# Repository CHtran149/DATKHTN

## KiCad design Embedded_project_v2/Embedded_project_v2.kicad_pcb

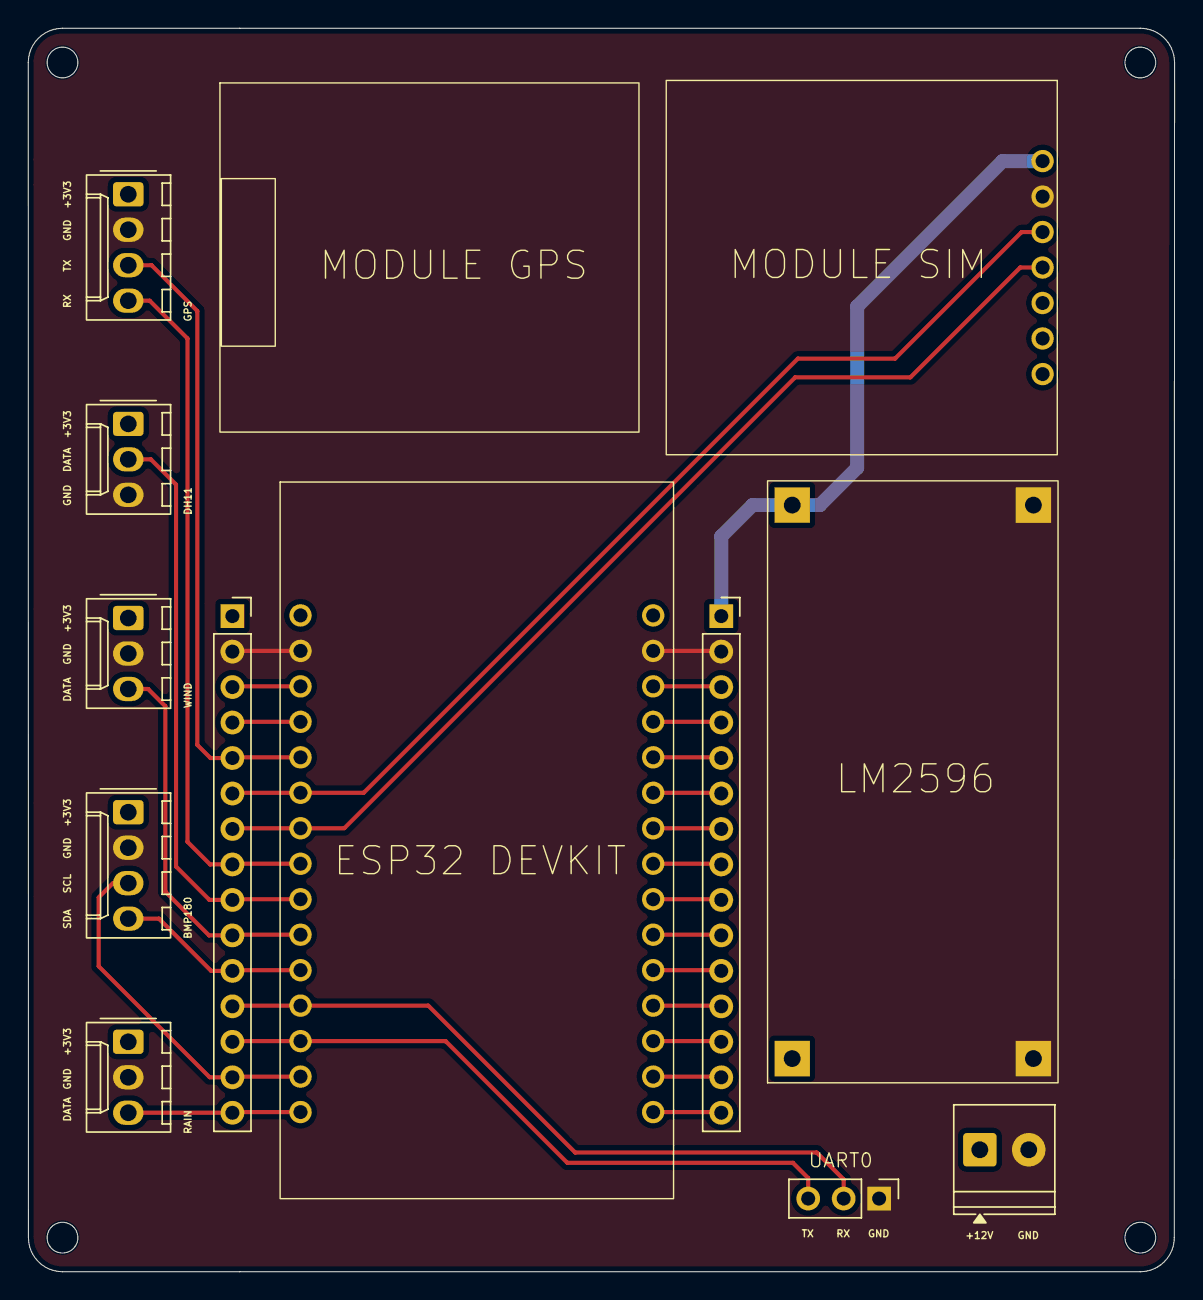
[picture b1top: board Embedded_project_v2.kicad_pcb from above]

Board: 2 copper layers, 82.1 x 89.0 mm, 12 parts (0 on the bottom side), 30 nets.

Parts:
J1: POWER IN; TerminalBlock_Phoenix_PT-1,5-2-3.5-H_1x02_P3.50mm_Horizontal
J2: TEMP,HUM SENSOR; Molex_KK-254_AE-6410-03A_1x03_P2.54mm_Vertical
J3: BMP180; Molex_KK-254_AE-6410-04A_1x04_P2.54mm_Vertical
J4: WIND SENSOR; Molex_KK-254_AE-6410-03A_1x03_P2.54mm_Vertical
J5: GPS; Molex_KK-254_AE-6410-04A_1x04_P2.54mm_Vertical
J6: RAIN SENSOR; Molex_KK-254_AE-6410-03A_1x03_P2.54mm_Vertical
J8, J9: Conn_01x15_Pin; PinSocket_1x15_P2.54mm_Vertical
J10: UART0; PinHeader_1x03_P2.54mm_Vertical
U1: Module LM2596
U2: DOIT_ESP32_DEVKIT_V1
U3: TDM-A7680C

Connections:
+3V3: J2.1, J3.1, J4.1, J5.1, J6.1, J8.1, U2.1 (3V3)
+5V: J9.1, U1.3 (OUT+), U2.16 (Vin), U3.1 (VCC)
+12V: J1.1, U1.1 (IN+)
/BMP180_SCL: J3.3, J8.14, U2.14 (D22)
/BMP180_SDA: J3.4, J8.11, U2.11 (D21)
/DHT11_DATA: J2.2, J8.9, U2.9 (D18)
/GMS_RX: J8.7, U2.7 (D17/TX2), U3.4 (RX)
/GMS_TX: J8.6, U2.6 (D16/RX2), U3.3 (TX)
/GPS_RX: J5.4, J8.8, U2.8 (D5)
/GPS_TX: J5.3, J8.5, U2.5 (D4)
/RAIN_DATA: J6.3, J8.15, U2.15 (D23)
/RX0: J8.12, J10.2, U2.12 (D3/RX0)
/TX0: J8.13, J10.3, U2.13 (D1/TX0)
/WIND_DATA: J4.3, J8.10, U2.10 (D19)
GND: J1.2, J2.3, J3.2, J4.2, J5.2, J6.2, J8.2, J9.2, J10.1, U1.2 (IN-), U1.4 (OUT-), U2.2 (GND), U2.17 (GND), U3.2 (GND)
unnamed: J8.3, U2.3 (D15)
unnamed: J8.4, U2.4 (D2)
unnamed: J9.3, U2.18 (D13)
unnamed: J9.4, U2.19 (D12)
unnamed: J9.5, U2.20 (D14)
unnamed: J9.6, U2.21 (D27)
unnamed: J9.7, U2.22 (D26)
unnamed: J9.8, U2.23 (D25)
unnamed: J9.9, U2.24 (D33)
unnamed: J9.10, U2.25 (D32)
unnamed: J9.11, U2.26 (D35)
unnamed: J9.12, U2.27 (D34)
unnamed: J9.13, U2.28 (D39/VN)
unnamed: J9.14, U2.29 (D36/VP)
unnamed: J9.15, U2.30 (EN)

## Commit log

2026-02-01 thêm code lần đầu tiên
2026-02-01 sửa lại cấu trúc code dự án
2026-02-03 Sửa lại Windspeed
2026-02-04 thêm task_sensor vào
2026-02-28 thêm task_processing
2026-02-28 Thêm 2 task là TaskFSM và TaskComm
2026-02-28 Chỉnh sửa Task_Comm
2026-03-02 thêm 2 task mới là TaskBlynk và TaskClould nhưng vẫn chưa hoàn thiện cần chỉnh sửa thêm
2026-03-12 Sửa lại thư viện GSM.h/.cpp và TaskComm.cpp (thêm yêu cầu 2 chiều từ SIM)
2026-03-12 TaskCould đang hoàn thiện
2026-03-13 sửa lại task_blynk và cập nhật dữ liệu lên app
2026-03-18 Đã chạy thành công hiển thị GPS lên log
2026-03-18 đưa GPS hiển thị lên blynk_app
2026-03-20 sửa thêm thư viện riêng và main.cpp
2026-03-25 thử và chạy thành công
2026-03-29 sửa phần request trong TaskComm
2026-03-29 đang hoàn thành task_comm
2026-03-29 thêm mới taskComm
2026-03-29 thêm gửi dữ liệu theo chu kì
2026-03-30 thay đổi wifi báo cáo
2026-04-01 thay đổi sơ đồ chân các cảm biến
2026-04-01 sửa lại thư viện cho GPS và đã chạy thành công
2026-04-02 đã gửi GMS thành công
2026-04-02 Thêm đặt ngưỡng cảnh báo bằng SMS chưa test.
2026-04-02 thêm chức năng gửi cả ngưỡng cảnh báo về trong TaskComm
2026-04-02 thay doi so dien thoai moi
2026-04-02 Cải thiện TaskComm về phần set ngưỡng
2026-04-02 TaskComm
2026-04-02 chỉnh sửa TaskComm và cả GSM.cpp
2026-04-02 Khắc phục lỗi thiếu dữ liệu khi SET và REQ
2026-04-05 triển khai task_cloud
2026-04-05 cập nhật task_cloud 5 phút gửi 1 lần
2026-05-09 thêm điều khiển từ blynk xuống hệ thống
2026-05-09 thay đổi 1 vài vấn đề cập nhật taskblynk, cloud,comm
2026-05-09 Đồng bộ ngưỡng của Blynk với Cloud
2026-05-09 Đồng bộ giữa task_comm và task_blynk (slider)
2026-05-13 điều chỉnh các thông số gửi lên gg sheet trong taskcloud
2026-05-13 Thêm WARN trong FSM
2026-05-13 thay đổi cách đồng bộ slider của blynk với SMS
2026-05-14 Đồng bộ giữa slider và task_comm
2026-05-15 sửa heatindex
2026-05-17 thêm pcb
2026-05-18 thay đổi core
